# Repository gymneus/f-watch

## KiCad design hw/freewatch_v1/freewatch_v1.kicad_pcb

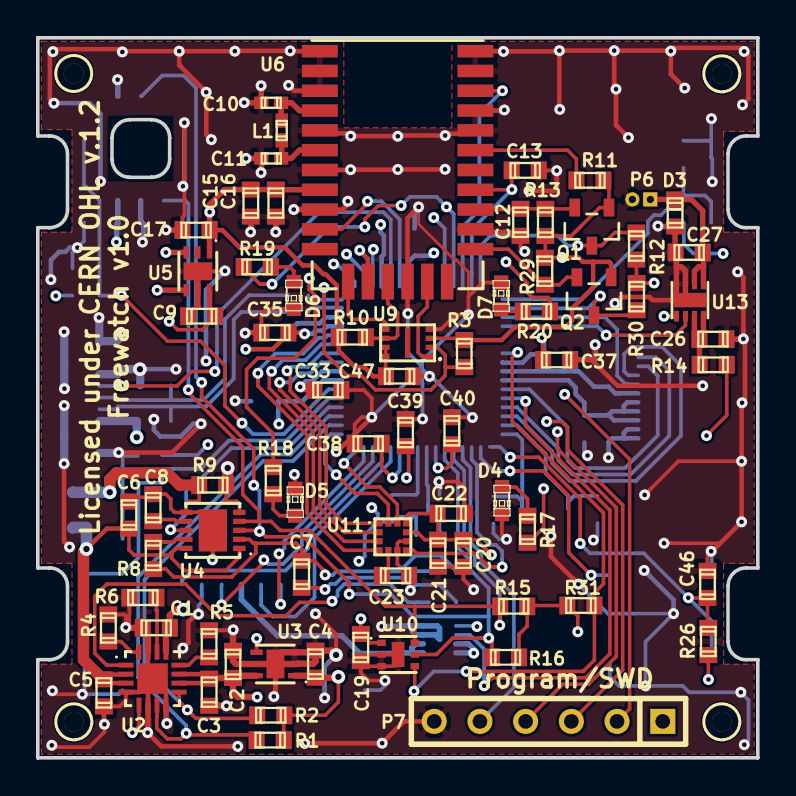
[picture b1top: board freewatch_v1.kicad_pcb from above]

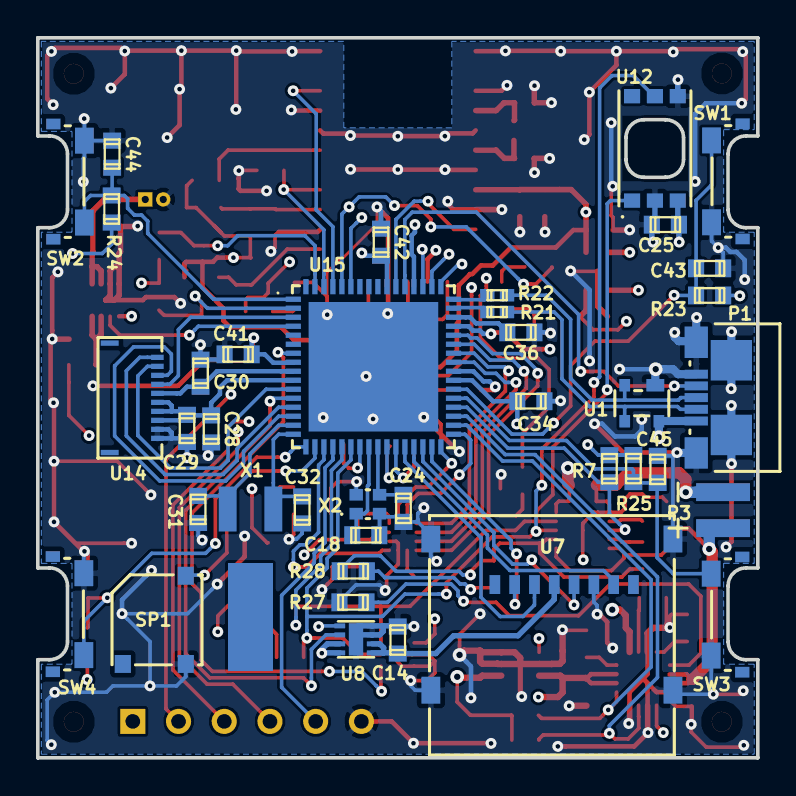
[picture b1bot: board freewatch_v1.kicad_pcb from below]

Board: 4 copper layers, 40.0 x 40.0 mm, 116 parts (39 on the bottom side), 83 nets.

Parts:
C1, C3, C9, C19, C28, C33, C36: 1uF; c_0603
C2, C4, C5, C17, C35: 4.7uF; c_0603
C6, C8, C14, C21, C22, C23, C25, C27, C29, C30, C34, C38, C39, C40, C41, C42, C43, C44, C45, C46, C47: 100nF; c_0603
C7: 10nF; c_0603
C10, C11: NM; c_0402
C12, C13, C16: 22pF; c_0603
C15: 2.2uF; c_0603
C18, C24: 10pF; c_0603
C20, C26, C37: 10uF; c_0603
C31, C32: 18pF; c_0603
D3: CDBU0130R; d_0603
D4, D5, D6, D7: LED_STD; LED-0603
HOLE_1.1MM, HOLE_1.1MM#2, HOLE_1.1MM#3, HOLE_1.1MM#4: VAL**; HOLE_1.1MM
L1: IND; c_0402
P1: USB-MICRO-AB; USB_MICRO_AB
P3: CONN_2; SMD_BAT_CONN
P6: CONN_2; CONN_1MM_2P
P7: CONN_6; SIL-6
Q1, Q2: BSS138; sot23
R1, R2, R23, R24, R25, R26, R31: 100k; r_0603
R3, R8, R10, R11, R12, R13, R27, R28, R29, R30: 10k; r_0603
R4, R5, R6: RES; r_0603
R7: 200k; r_0603
R9: 10m; r_0603
R14: 10R; r_0603
R15, R16: 3k3; r_0603
R17, R18, R19, R20: 91R; r_0603
R21, R22: 15R; c_0402
SP1: BUZZER; BUZZER_SMT-0540-S-R
SW1, SW2, SW3, SW4: EVQ-P4MB3K; SWITCH_EVQP4
U1: PRTR5V0U2X; SOT143B
U2: bq24072; S-PVQFN-N16
U3, U5: TPS780180300; SON-6
U4: MAX17047; TDFN-10
U6: M10478-A1
U7: MICRO_SDCARD_SPI; CONN_MICRO_SDCARD_1010030368
U8, U13: ADP198; LFCSP_8L
U9: SST25WF040B; USON_2X3
U10: MAX44009; UTDFN6_OPTO
U11: LSM303C; LGA12
U12: MS5806-02BA
U14: LS013B7DH03; FPC_10_503480-1000
U15: EFM32GG330; QFN64
X1: 32.768kHz; AB26TRB
X2: 48MHz; ABM11_CRYSTAL

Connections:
+1.8V: C15.1, C16.1, C17.1, C47.1, Q1.1, Q2.1, R3.2, R10.2, R11.2, R13.2, R29.2, U5.1, U6.8, U9.3, U9.7, U9.8
+5V: C1.1, C35.1, P1.1, U1.4, U2.13, U15.45, U15.52
+BATT: C5.1, C6.1, P3.1, U2.2, U2.3, U4.1, U4.10
+VIN: C2.1, C3.1, C9.1, R14.1, U2.5, U2.10, U2.11, U3.4, U3.6, U5.3, U5.4, U5.6
/MCU_DISPLAY/BUZ: SP1.1, U15.18
/MCU_DISPLAY/LCD_BKL1: R19.1, R20.1, U15.60
/MCU_DISPLAY/LCD_BKL2: R17.1, R18.1, U15.59
/MCU_DISPLAY/LCD_CLK: U14.1, U15.13
/MCU_DISPLAY/LCD_CS: U14.3, U15.14
/MCU_DISPLAY/LCD_DI: U14.2, U15.11
/MCU_DISPLAY/LCD_EN: C30.1, U14.5, U15.9
/MCU_DISPLAY/LCD_INV: U14.4, U15.3
/MCU_DISPLAY/LCD_VCC: C28.1, C29.1, U14.6, U14.7, U14.8, U15.10
/MCU_DISPLAY/MCU_RST_N: P7.5, U15.20
/MCU_DISPLAY/SWCLK: P7.3, U15.49
/MCU_DISPLAY/SWDIO: P7.2, U15.50
/MCU_DISPLAY/SWDO: P7.4, U15.51
/MCU_DISPLAY/SW_BL: C45.1, R25.2, SW3.2, U15.37
/MCU_DISPLAY/SW_BR: C46.1, R26.2, SW4.2, U15.17
/MCU_DISPLAY/SW_TL: C43.1, R23.2, SW1.2, U15.38
/MCU_DISPLAY/SW_TR: C44.1, R24.2, SW2.2, U15.1
AC_CLK: U11.1, U15.42
AC_CS_MAG: U11.3, U15.43
AC_CS_XL: U11.2, U15.41
AC_DRDY_MAG: U11.11, U15.32
AC_INT_MAG: U11.7, U15.19
AC_INT_XL: U11.12, U15.33
AC_SDIO: U11.4, U15.44
BC_CHG_N: R2.1, U2.9, U15.34
BC_PGOOD_N: R1.1, U2.7, U15.35
FG_ALRT_N: R7.1, U4.8, U15.36
GND: C1.2, C2.2, C3.2, C4.2, C5.2, C9.2, C10.2, C11.2, C12.2, C13.2, C14.2, C15.2, C16.2, C17.2, C18.2, C19.2, C20.2, C21.2, C22.2, C23.2, C24.2, C25.2, C26.2, C27.2, C28.2, C29.2, C30.2, C31.1, C32.1, C33.2, C34.2, C35.2, C36.2, C37.2, C38.2, C39.2, C40.2, C41.2, C42.2, C43.2, C44.2, C45.2, C46.2, C47.2, D3.1, D4.2, D5.2, D6.2, D7.2, P1.5, P1.6, P1.7, P1.8, P1.9, P6.2, P7.6, R4.1, R5.1, R6.1, R9.2, R27.1, SP1.2, SW1.1, SW2.1, SW3.1, SW4.1, U1.1, U2.4, U2.6, U2.8, U2.15, U2.17, U3.2, U3.3, U3.5, U3.7, U4.5, U5.5, U5.7, U6.1, U6.2, U6.3, U6.5, U6.7, U6.9, U6.15, U6.19, U6.24, U6.25, U6.27, U6.28, U7.6, U7.9, U8.0, U8.3, U8.4, U9.4, U10.0, U10.2, U10.3, U11.6, U11.8, U12.2, U12.4, U13.0, U13.3, U13.4, U14.9, U14.10, U15.0, X2.3
GPS_ON_OFF: U6.26, U15.61
GPS_RST: U6.10, U15.54
GPS_RXD: C13.1, U6.21, U15.62
GPS_TXD: Q1.3, R12.1, U15.63
GPS_WAKUP: Q2.3, R30.1, U15.2
LS_INT_N: R31.1, U10.4, U15.7
unnamed: C6.2, C7.2, C8.2, P3.2, R9.1, R28.1, U4.6, U4.11
unnamed: C7.1, R8.1, R28.2, U4.2
unnamed: C8.1, U4.7
unnamed: C10.1, L1.1, U6.4
unnamed: C11.1, L1.2, U6.6
unnamed: C12.1, Q1.2, R13.1, U6.20
unnamed: C14.1, U7.4, U8.1, U8.2
unnamed: C18.1, U15.24, X2.1
unnamed: C23.1, U11.5
unnamed: C24.1, U15.25, X2.2
unnamed: C26.1, R14.2, U13.7, U13.8
unnamed: C27.1, D3.2, P6.1, U13.1, U13.2
unnamed: C31.2, U15.15, X1.1
unnamed: C32.2, U15.16, X1.2
unnamed: C33.1, U15.40
unnamed: C36.1, U15.46
unnamed: D4.1, R17.2
unnamed: D5.1, R18.2
unnamed: D6.1, R19.2
unnamed: D7.1, R20.2
unnamed: Q2.2, R29.1, U6.18
unnamed: R3.1, U6.13, U9.2
unnamed: R4.2, U2.16
unnamed: R5.2, U2.12
unnamed: R6.2, U2.14
unnamed: R8.2, U4.9
unnamed: R10.1, U6.14, U9.6
unnamed: R11.1, U6.23
unnamed: R21.2, U15.47
unnamed: R22.2, U15.48
unnamed: R27.2, U2.1
unnamed: U6.12, U9.5
unnamed: U6.16, U9.1
SCL: R16.2, U4.3, U10.5, U12.5, U15.22
SDA: R15.2, U4.4, U10.6, U12.1, U15.21
SD_CLK: U7.5, U15.30
SD_CS_N: U7.2, U15.31
SD_EN: U8.6, U15.12
SD_MISO: U7.7, U15.29
SD_MOSI: U7.3, U15.28
USB_DM: P1.2, R21.1, U1.3
USB_DP: P1.3, R22.1, U1.2
USB_ID: P1.4, U15.53
VCC: C4.1, C19.1, C20.1, C21.1, C22.1, C25.1, C34.1, C37.1, C38.1, C39.1, C40.1, C41.1, C42.1, P7.1, R1.2, R2.2, R7.2, R12.2, R15.1, R16.1, R23.1, R24.1, R25.1, R26.1, R30.2, R31.2, U3.1, U8.5, U8.7, U8.8, U10.1, U11.9, U11.10, U12.3, U13.5, U15.8, U15.23, U15.26, U15.27, U15.39, U15.55
VM_EN: U13.6, U15.4

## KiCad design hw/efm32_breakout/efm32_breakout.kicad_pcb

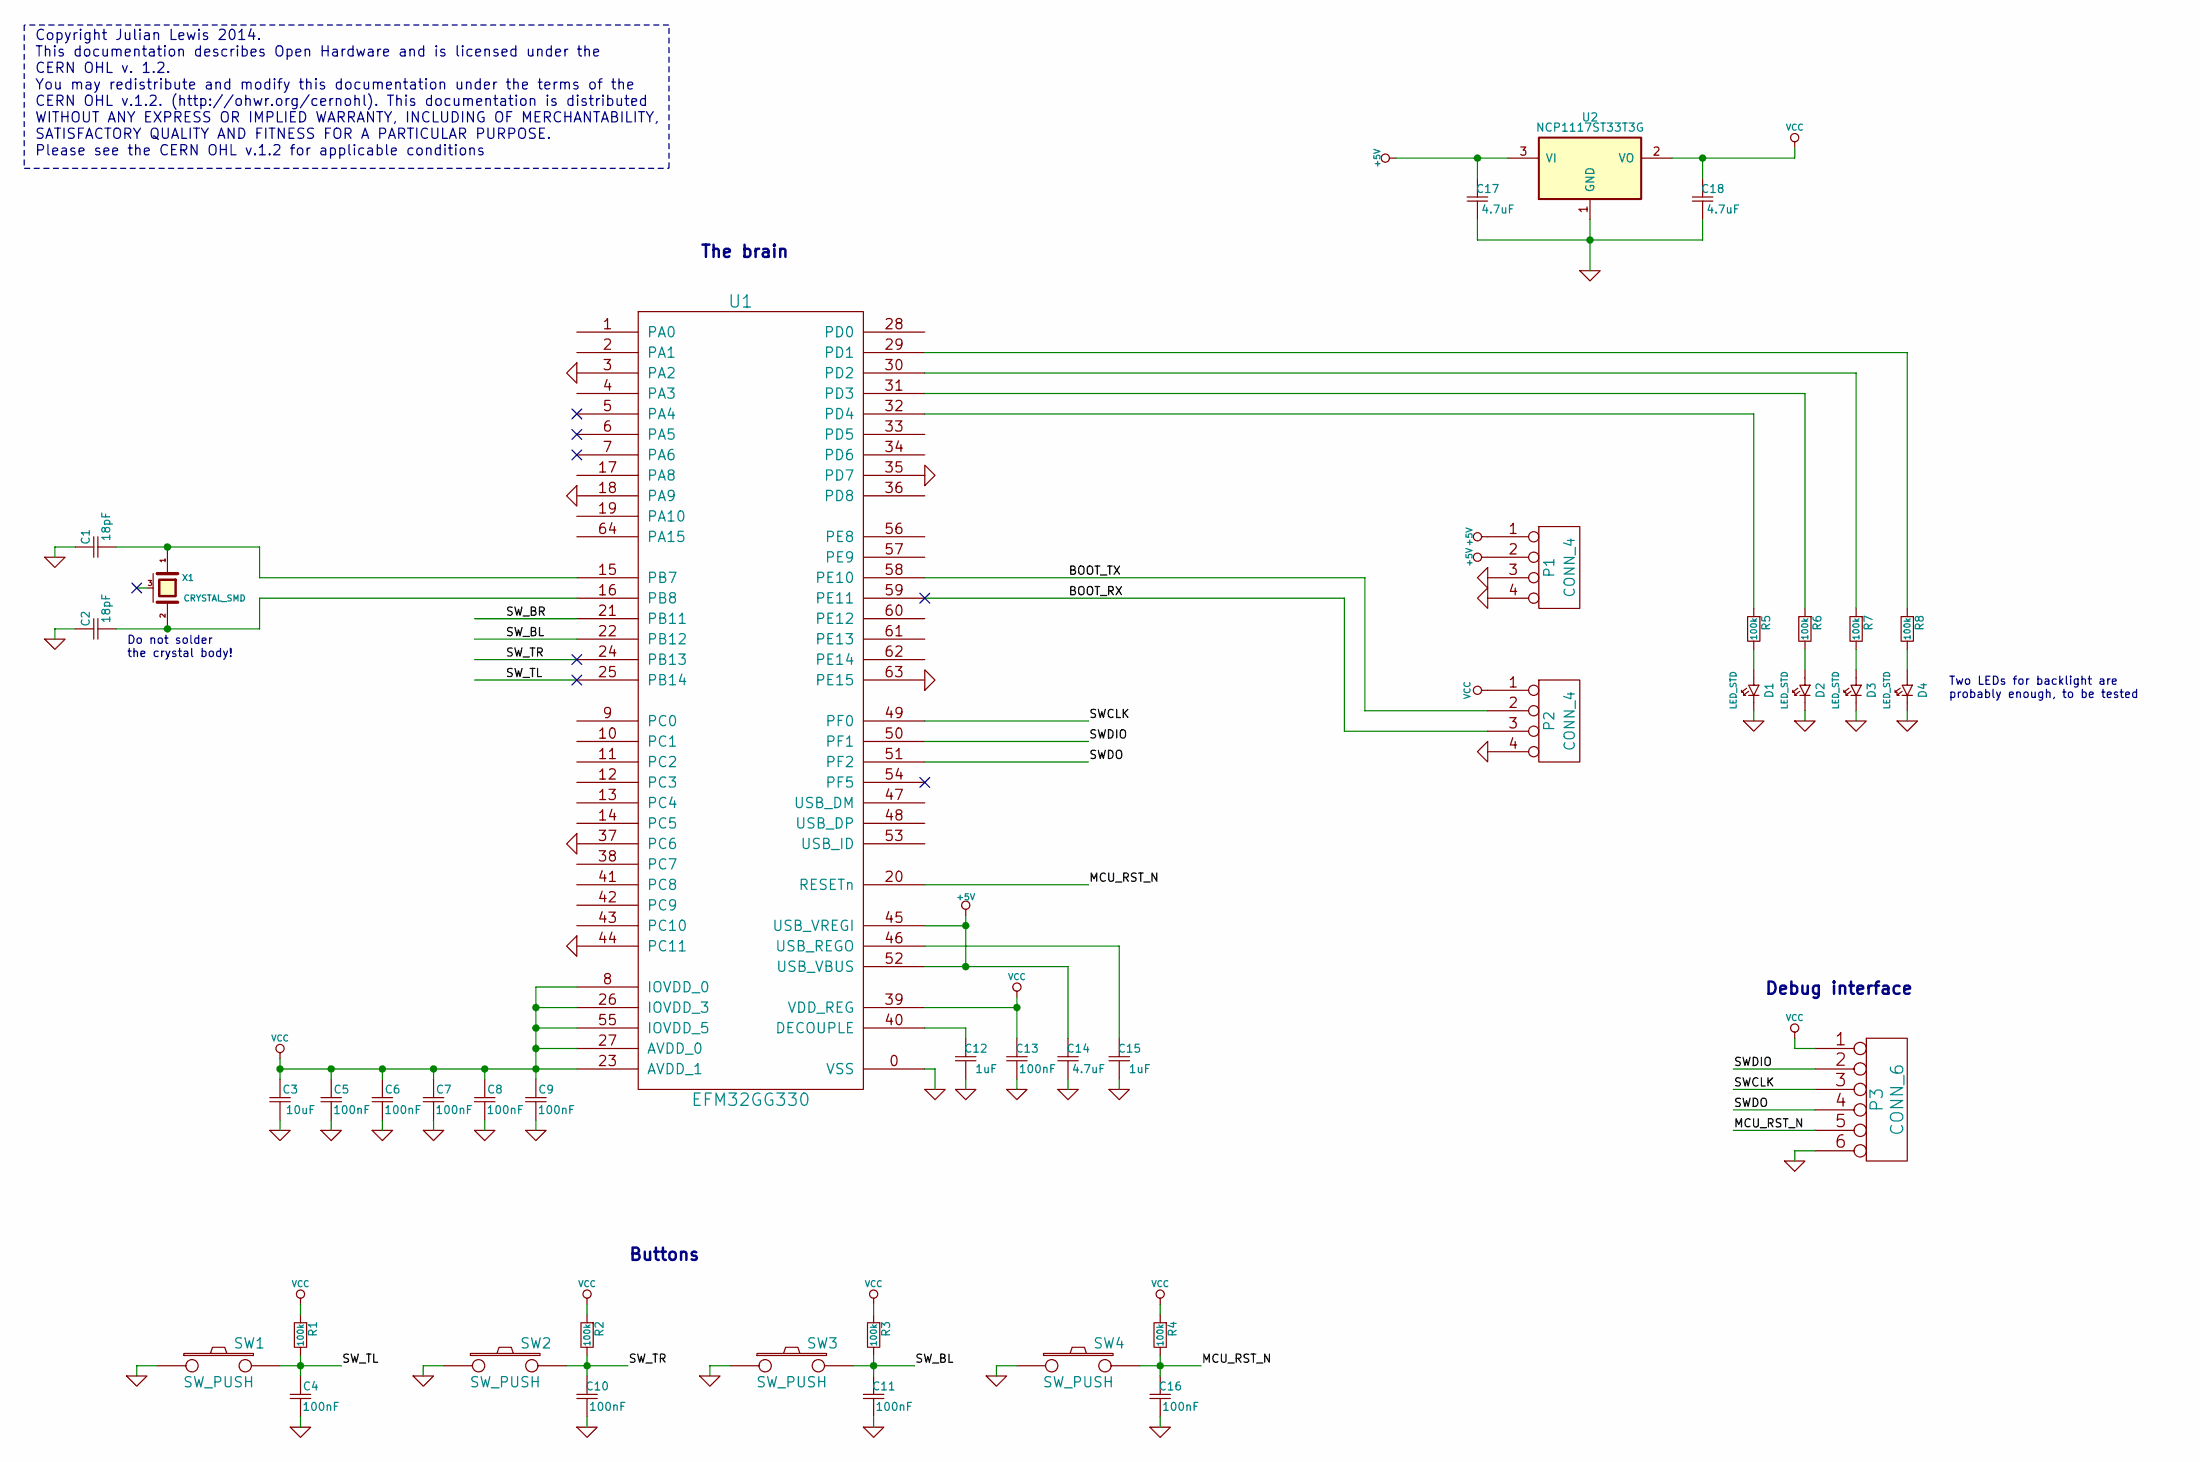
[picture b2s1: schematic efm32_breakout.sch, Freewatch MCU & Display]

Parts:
C1, C2: 18pF
C3: 10uF
C4, C5, C6, C7, C8, C9, C10, C11, C13, C16: 100nF
C12, C15: 1uF
C14, C17, C18: 4.7uF
D1, D2, D3, D4: LED_STD
P1, P2: CONN_4
P3: CONN_6
R1, R2, R3, R4, R5, R6, R7, R8: 100k
SW1, SW2, SW3, SW4: SW_PUSH
U1: EFM32GG330
U2: NCP1117ST33T3G
X1: CRYSTAL_SMD

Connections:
+5V: C14.1, C17.1, P1.1, P1.2, U1.45 (USB_VREGI), U1.52 (USB_VBUS), U2.3 (VI)
/BOOT_RX: P2.3, U1.59 (PE11)
/BOOT_TX: P2.2, U1.58 (PE10)
/MCU_RST_N: C16.1, P3.5, R4.2, SW4.2, U1.20 (RESETn)
/SWCLK: P3.3, U1.49 (PF0)
/SWDIO: P3.2, U1.50 (PF1)
/SWDO: P3.4, U1.51 (PF2)
/SW_BL: C11.1, R3.2, SW3.2, U1.22 (PB12)
/SW_BR: U1.21 (PB11)
/SW_TL: C4.1, R1.2, SW1.2, U1.25 (PB14)
/SW_TR: C10.1, R2.2, SW2.2, U1.24 (PB13)
GND: C1.1, C2.1, C3.2, C4.2, C5.2, C6.2, C7.2, C8.2, C9.2, C10.2, C11.2, C12.2, C13.2, C14.2, C15.2, C16.2, C17.2, C18.2, D1.2 (K), D2.2 (K), D3.2 (K), D4.2 (K), P1.3, P1.4, P2.4, P3.6, SW1.1, SW2.1, SW3.1, SW4.1, U1.0 (VSS), U1.3 (PA2), U1.18 (PA9), U1.35 (PD7), U1.37 (PC6), U1.44 (PC11), U1.63 (PE15), U2.1 (GND)
unnamed: C1.2, U1.15 (PB7), X1.1
unnamed: C2.2, U1.16 (PB8), X1.2
unnamed: C12.1, U1.40 (DECOUPLE)
unnamed: C15.1, U1.46 (USB_REGO)
unnamed: D1.1 (A), R5.2
unnamed: D2.1 (A), R6.2
unnamed: D3.1 (A), R7.2
unnamed: D4.1 (A), R8.2
unnamed: R5.1, U1.32 (PD4)
unnamed: R6.1, U1.31 (PD3)
unnamed: R7.1, U1.30 (PD2)
unnamed: R8.1, U1.29 (PD1)
VCC: C3.1, C5.1, C6.1, C7.1, C8.1, C9.1, C13.1, C18.1, P2.1, P3.1, R1.1, R2.1, R3.1, R4.1, U1.8 (IOVDD_0), U1.23 (AVDD_1), U1.26 (IOVDD_3), U1.27 (AVDD_0), U1.39 (VDD_REG), U1.55 (IOVDD_5), U2.2 (VO)

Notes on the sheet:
Copyright Julian Lewis 2014. This documentation describes Open Hardware and is licensed under the CERN OHL v. 1.2. You may redistribute and modify this documentation under the terms of the CERN OHL v.1.2. (http://ohwr.org/cernohl). This documentation is distributed WITHOUT ANY EXPRESS OR IMPLIED WA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
Do not solder the crystal body!
Debug interface
Buttons
The brain
Two LEDs for backlight are probably enough, to be tested

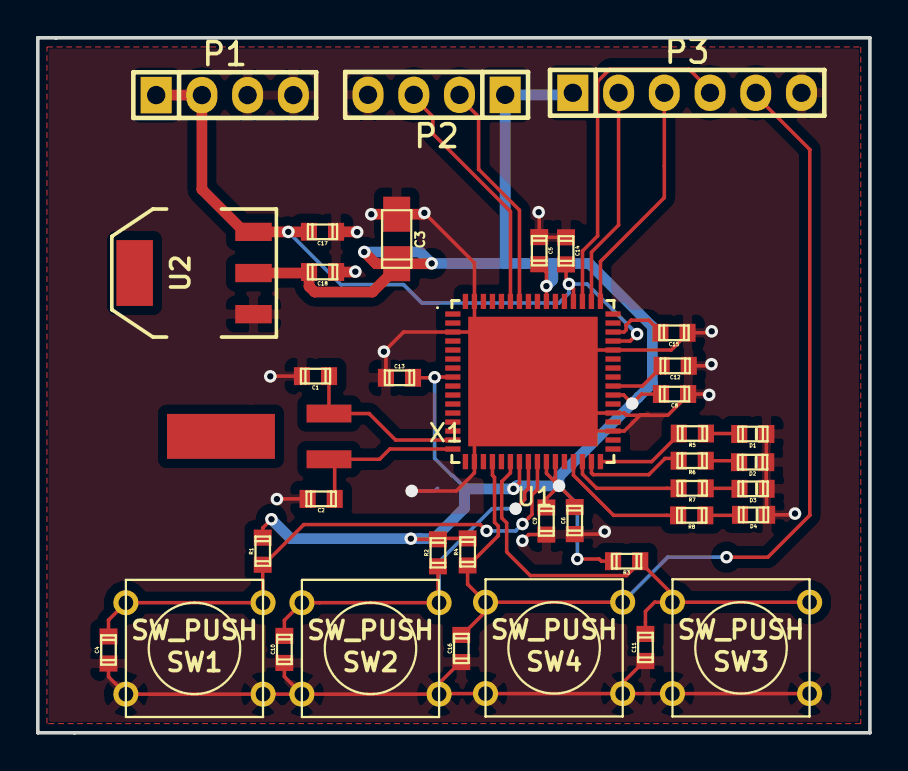
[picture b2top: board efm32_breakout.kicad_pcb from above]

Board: 2 copper layers, 46.2 x 38.6 mm, 40 parts (1 on the bottom side), 24 nets.

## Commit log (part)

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2014-08-25 ui: Added functions for clearing.
2014-08-25 Fixed infinite queue of random events.
2014-08-25 Extra fonts.
2014-08-25 Rotated LCD screen.
2014-08-25 Initial version of clock application based on UI library.
2014-08-25 Renamed Application to application.
2014-08-25 gfx: Text can drawn using either black or white pixels.
2014-08-25 menu & clock: Remapped buttons.
2014-08-25 freertos: Increased the minimal stack size.
2014-08-25 menu: Just a few comments.
2014-08-25 menu: Displays a fake list of application. It is possible to switch between menu & clock screens.
2014-08-25 menu: Scrollable, if too long to be displayed on one screen.
2014-08-25 sw: add altitude to pressure helper function and example for altitude calibration.
2014-08-26 Add drivers folder and move GPS and USB functions
2014-08-26 Pulled drivers from Orson's branch
2014-08-26 lcd: Fixed off-by-one error.
2014-08-26 rtc: Sends tick events. Sleep mode has been temporarily reduced to EM1.
2014-08-26 Playing around with the LCD
2014-08-26 gfx: Merged bitmap drawing routines.
2014-08-26 menu: Entries have icons.
2014-08-26 menu: Moved unnecessary headers to a single file (app_list.h).
2014-08-26 gpsapp: Implement gps_event and gps_redraw
    Note: still standalone, 'bear'-metal application, not yet hooked
    to FreeRTOS
2014-08-26 apps: Removed unnecessary header file.
2014-08-26 gps-lib: Reduced number of params on some fcns
2014-08-26 gpsapp: Now displays UTC time from GPS
2014-08-26 Checkout GFX files (bitmap fcn)
2014-08-27 gps: Moving things around in the UI
2014-08-27 sw: work on pressure graph display (still buggy).
2014-08-27 sw: kind of working graph display (should be improved and generalised as a widget).
2014-08-28 Add GPS icon to status bar
2014-08-28 Working towards displaying GPS coords on app screen
2014-08-29 gpscoord: Printing all coordinates in one format on screen
2014-08-29 lcd: EXTCOMIN signal is directly controlled by a timer.
2014-08-30 buzzer: Driver, basic routines. Updated the example application.
2014-08-30 lcd: Rotated extra 180 degrees.
2014-08-30 buttons: Rotated 180 degrees to match the current LCD display mode.
2014-08-30 acc/mag driver: fixed and filled with read/write spi functions
2014-08-30 LSM303C: update old driver spi calls
2014-08-30 acc/mag: wip
2014-08-30 adding LSM303C accelerometer and compass driver from ST
    Initial commit, functions to read/write registers still to be filled.
2014-08-30 lightweight printf implementation taken from wrpc-sw
2014-08-30 lsm303: adding python log analyzer for simple hard/soft-iron calibration
2014-08-31 gfx: Fix warnings.
2014-08-31 buzzer: Extend comments.
2014-08-31 makefile: Corrected debug flags.
2014-08-31 menu: Fixed scrolling bug.
2014-08-31 menu & status_bar: Added a few defines for dimensions.
2014-09-01 Add Reset app
2014-09-02 Trying to add bootloader
2014-09-03 lcd: DMA mode
2014-09-03 mec: add glass text design and howto create kicad module from bitmap.
2014-09-03 hw: add glass text to module library.
2014-09-04 magnetometer & compass: Interrupt events are supported (*not tested yet*).
2014-09-06 efm32_hello: use freewatch_utils
2014-09-06 Moving to Fede's branch to check bootloader code
2014-09-07 Add bootloader files from Fede's branch
    Broke one button, attempting to change files accordingly.
2014-09-08 doc: add flyer and icons.
2014-09-08 freertos: Automatic backlight adjustment (has to be calibrated).
2014-09-08 lcd: Fixed the tearing effect (at least in FreeRTOS).
2014-09-09 freertos: State handler (automatically disables the backlight after a period of inactivity).
2014-09-11 compass: wip
2014-09-11 drivers/lcd: go back to proper LCD orientation
2014-09-11 sincos: calculate sin/cos for full -360/360 deg range
2014-09-11 adding compass app
2014-09-11 sincos: small fix to ABS macro
2014-09-14 Work towards SW_BL enables load new firmware mode
    Tested, but not yet working. SW_BL makes loop pass, but no USB connection yet.
2014-09-17 gpx: Small fixes to make GPX files importable into, e.g., OpenStreetMap
    Some of the GPX end tags were missing the '/' corresponding to XML end tags
    and this meant websites such as OpenStreetMap [1] or MapBBCode [2] could not
    import the GPX files created using test_covert_files.
    The tags were added and now these sites can import our GPX traces.
    [1] openstreetmap.org
    [2] http://share.mapbbcode.org
2014-09-17 ui: Added spinbox widget.
2014-09-17 ui: Added 'set time' application.
2014-09-18 gpscoord: Testing
2014-09-18 ui: Added 'set date' application.
2014-09-20 lcd: A few comments.
2014-09-20 settings: Limited choice in spinboxes to sensible values.
2014-09-21 i2c: Transfers are synchronized using semaphores.
2014-09-23 ui: Experimental battery status icon.
2014-09-23 bootloader: FreeRTOS app now boots properly
    The issue was the SysTick timer, which was configured by the bootloader to
    blink the backlight LEDs, but was not de-configured before booting to the
    application.
    Without the SysTick timer de-configured, the FreeRTOS tick timer, which relies
    on the SysTick timer, fired before FreeRTOS could be properly configured. Since
    the FreeRTOS SysTick handler contains some OS-specific functions and data, the
2014-09-24 bootloader: FreeRTOS app now boots properly
    The issue was the SysTick timer, which was configured by the bootloader to
    blink the backlight LEDs, but was not de-configured before booting to the
    application.
    Without the SysTick timer de-configured, the FreeRTOS tick timer, which relies
    on the SysTick timer, fired before FreeRTOS could be properly configured. Since
    the FreeRTOS SysTick handler contains some OS-specific functions and data, the
2014-09-25 fix copyright headers
2014-09-25 fixing bitmaps, for some reason bmp2rle could not open few bitmaps, opening with gimp and saving without any changes helped
2014-09-26 sw: Add FreeRTOS blink project
2014-09-26 sw: FreeRTOS blinky up and running
2014-09-26 sw: Removed OS comparison Win projects`
2014-09-26 sw : a test from xavier
2014-09-26 sw : cpying roject freertos_blink_fat as a copy of freertos_blink + integration of FAT-SL now it doesn't produce a valid binary (compliation is ok but file is too big)
2014-09-26 fixing SPI specificities for freewatch
2014-09-26 added SPI implementation provided by EnergyMicro , created file for implementing driver FAT on SD through SPI
2014-09-26 sw : test from xavier removed
2014-09-26 converter from GPS data to raw data to store in a file on the SD converter reverse (from raw data from file to GPS data) converter from GPS data to GPX format
2014-09-26 SD via SPI : now the basic is done (init of the card, need to test read and write functions)
2014-09-26 The SPI drivers works (we see expected stuff with data analyzer)
2014-09-26 working on implementation of SD driver throug SPI
2014-09-26 SD via SPI : works thanks to efm32 implementation. We use fatfs to implement FAT32 (instead of FAT-SL) Project sw/os-comparison/an0030_efm32_fat_on_sd_card compiles and run the FAT32 : it writes a fi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
2014-09-26 SD protocol on SPI have a first implementation
2014-09-27 sw: Make altimeter test work with dma lcd.
2014-09-27 usbdmsd: Add USB mass storage device test project and MSD drivers.
2014-09-28 sw: use bigger font for clock.
2014-09-28 Initial commit for FreeRTOS.
2014-09-28 hw: add waterproof usb connector footprint, work on v2 schematics.
2014-09-28 Update .gitignore rules.
2014-09-28 Added an example application (button tester).
2014-09-28 menu: Fixed scrolling through the menu.
2014-09-28 sw: work on path widget (total crap for now).
2014-09-28 Updated licenses.
2014-09-28 Work towards optimizing GPS application
2014-09-29 move lsm303c driver, we won't use the one from ST
2014-09-30 bootloader: Removed a potential debug lock.
2014-10-01 More trials with GPS optimization
    A bug was fixed in gps_parse_nmea(), whereby the wrong buffer was
    given as a param to strlen(), which is used in gps_parse_nmea() to
    provide a buffer size parameter to nmea_parse.
    After this, the processor now enters a hard fault ,probably due to
    segmentation fault. More debug is needed probably with a different
    board to find out why.
2014-10-01 Debugging in progress on GPS optimization
2014-10-02 Added FreeRTOS assert and linked it to NMEA_ASSERT()
2014-10-02 sw: Change a bit randomlly generated test data for path widget.
2014-10-03 Add GPS libraries
2014-10-03 Added menu wrap-around
2014-10-03 Moved usbdbg_init() before other init functions
2014-10-04 Move reset app to src/apps/ and add HardFault_Handler
2014-10-04 Check for GPS on in status bar handler
2014-10-04 Add GPS background `task' and make changes accordingly
    Two more events were added to the event type (event.h)
    - GPS_TICK -- tick from GPS background task
    - GPS_OFF -- to signal the status bar that the GPS was turned off,
    so it can remove the icon
    The status bar and GPS coordinate app were changed to react to the
    proper events, i.e., both events above in the case of the status bar
2014-10-04 gpsdrv: Made gps_get_utc() return year since 1900, month since Jan
    Previously, this function was returning a human-friendly version of the
    time received from GPS. This was now optimized to make it easire to operate
    with other programming structures (e.g., struct tm). This modification has the
    added benefit of returning the exact values received via the GPRMC NMEA
    sentence.
2014-10-04 Add "app" to manually set time from GPS
    This app is not yet properly working, it doesn't always properly set time.
    To be checked out exactly why.
2014-10-04 Made spinbox wrap around
2014-10-05 Time setting from GPS now works, still having problems with date setting
2014-10-05 Added GPS settings submenu
2014-10-05 Fixed date setting from GPS
2014-10-05 Added ui_update() as default event behaviour in settings apps
2014-10-05 Using USB debug only when DEBUG symbol is set
2014-10-05 freertos: Enable configUSE_TICKLESS_IDLE.
2014-10-05 compass: Removed the status bar (the app is now fullscreen).
2014-10-05 compass: Disabled the calibration.
2014-10-05 Store settings to flash
2014-10-05 Add blobify script
2014-10-06 Use TR button to exit from USB mass storage app
    All other apps use the same button to exit, so the USB mass storage app was
    changed in kind.
2014-10-06 Slight aesthetic changes
2014-10-06 Fixed non-working GPS module in release mode
    The bloody compiler optimization was screwing over NMEA parsing, which made the
    GPS not work anymore.
    Thank you GCC for taking away 2 hrs of my life, just like that: POOF!
2014-10-07 Implemented GPS tracking
2014-10-07 Fixed some warnings.
2014-10-07 Fix score overflows in the ball game.
2014-10-07 Fixed xQueueReceive() ticks-to-wait parameter in tasks.
2014-10-07 Fixed switching between coordinates and elevation in gps_coord.
2014-10-07 lcd: Disable DMA transfers depending on the power saving mode.
2014-10-07 EM2 enabled.
2014-10-07 Always initialize variables!
2014-10-07 Work towards reliable GPS trace storage, not there yet.
    work:
    - configured FatFs to support long file names
    - configured FreeRTOS for max sleep mode = EM1 (this makes the GPS work with the
    OS putting the MCU in sleep mode)
    - set optimization level to -O0, to make the accelerometer and compass work
    - fooling around in GPS background task to try to store GPS trace
2014-10-08 ixed DEG MIN SEC display and changed headers to gpslib files
2014-10-08 Commented GPS library code
2014-10-08 set_date: Fixed setting years.
2014-10-08 Time settings fix.
2014-10-08 Changing to new task doing the tracking
2014-10-09 Removed test projects, copied freertos to freewatch
    The test projects are now in the test-projects branch
2014-10-09 doc: Update url on flyer.
2014-10-11 Added license headers in various source files
2014-10-11 Removed unused files.
2014-10-11 added LICENSE and AUTHORS file to the mec/ folder
2015-01-12 Added code for GPS tracking in background task. Doesn't work yet.
2015-01-20 Regenerated usb_ms_icon.bmp
2015-02-09 Added checking of GPS WAKEUP pin
2015-02-09 Fixed non-storing tracking setting
2015-02-09 Improved tracking icon
2015-02-09 Changed GPS fix status storage in GPS driver
2015-02-09 Added tracking icon when option is set
2015-02-09 Coordinate storage to SD card seems to be working
    More testing to be done to confirm it is working properly.
2015-02-09 Trying to add tracking icon, not successful yet
2015-02-09 Added turn off of GPS prior to reset

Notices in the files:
hw/freewatch_v1/freewatch_v1.kicad_pcb:
Licensed under CERN OHL v.1.2
